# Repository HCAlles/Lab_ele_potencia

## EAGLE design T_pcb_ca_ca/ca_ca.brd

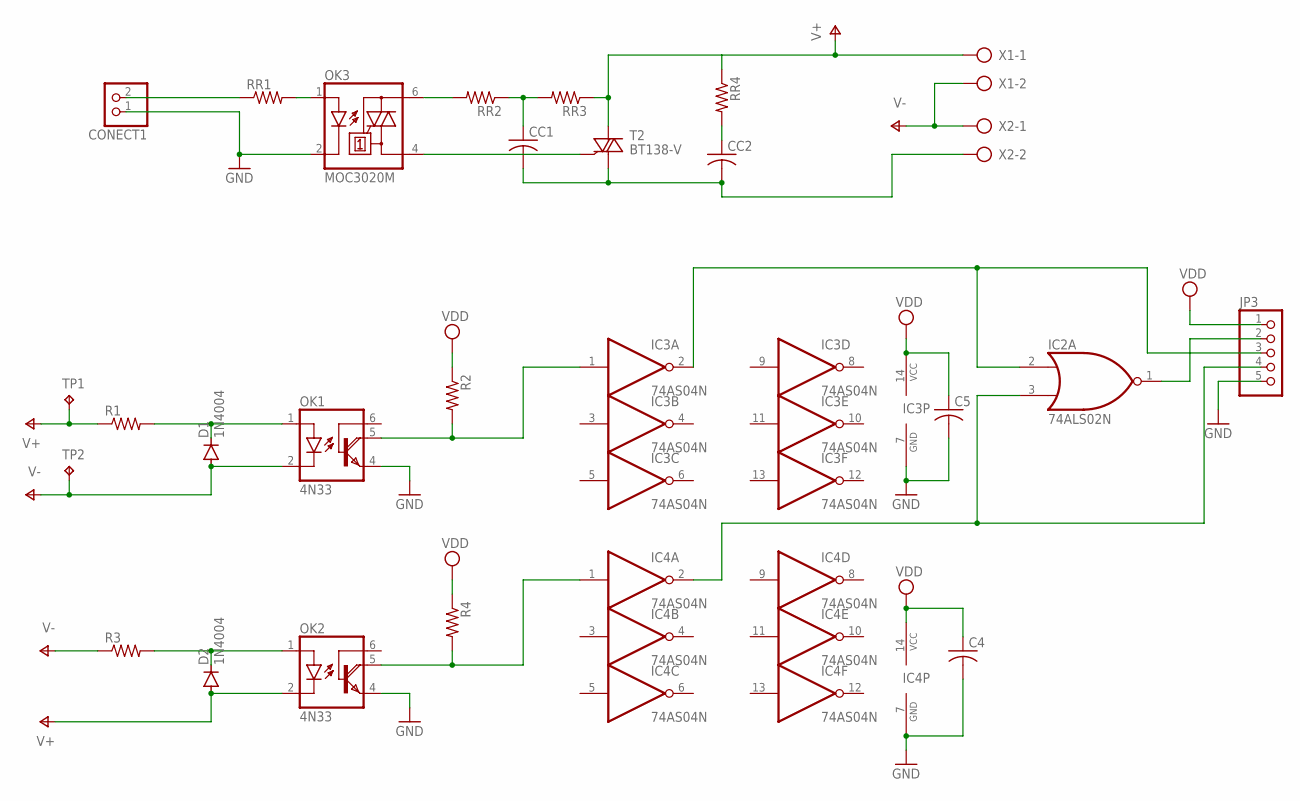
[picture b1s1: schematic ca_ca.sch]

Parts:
C4, C5: C-US102-064X133; C102-064X133
CC1, CC2: C-US102-064X133; C102-064X133
CONECT1: PINHD-1X2; 1X02
D1, D2: 1N4004; DO41-10
IC2: 74ALS02N; DIL14
IC3, IC4: 74AS04N; DIL14
JP3: PINHD-1X5; 1X05
OK1, OK2: 4N33; DIL06
OK3: MOC3020M; DIL06
R1, R2, R3, R4: R-US_0617/22; 0617/22
RR1, RR2, RR3, RR4: R-US_0617/22; 0617/22
T2: BT138-V; TO220BV
TP1, TP2: TPPAD1-17Y; P1-17Y
X1, X2: AK500/2-H

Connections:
GND: C4.2, C5.2, CONECT1.1, IC2.7 (GND), IC3.7 (GND), IC4.7 (GND), JP3.5, OK1.4 (E), OK2.4 (E), OK3.2 (C)
unnamed: OK3.1 (A), RR1.2
unnamed: CONECT1.2, RR1.1
unnamed: OK3.4 (A1), T2.G
unnamed: CC1.1, RR2.1, RR3.2
unnamed: OK3.6 (A2), RR2.2
unnamed: IC3.1 (I), OK1.5 (COL), R2.2
unnamed: CC1.2, CC2.2, T2.T1 (A1), X2.2
unnamed: CC2.1, RR4.2
unnamed: D1.C, OK1.1 (A), R1.2
unnamed: IC2.2 (I0), IC3.2 (O), JP3.3
unnamed: IC4.1 (I), OK2.5 (COL), R4.2
unnamed: D2.C, OK2.1 (A), R3.2
unnamed: IC2.3 (I1), IC4.2 (O), JP3.4
unnamed: IC2.1 (O), JP3.2
V+: D2.A, OK2.2 (C), R1.1, RR3.1, RR4.1, T2.T2 (A2), TP1.TP, X1.1
V-: D1.A, OK1.2 (C), R3.1, TP2.TP, X1.2, X2.1
VCC: IC2.14 (VCC)
VDD: C4.1, C5.1, IC3.14 (VCC), IC4.14 (VCC), JP3.1, R2.1, R4.1

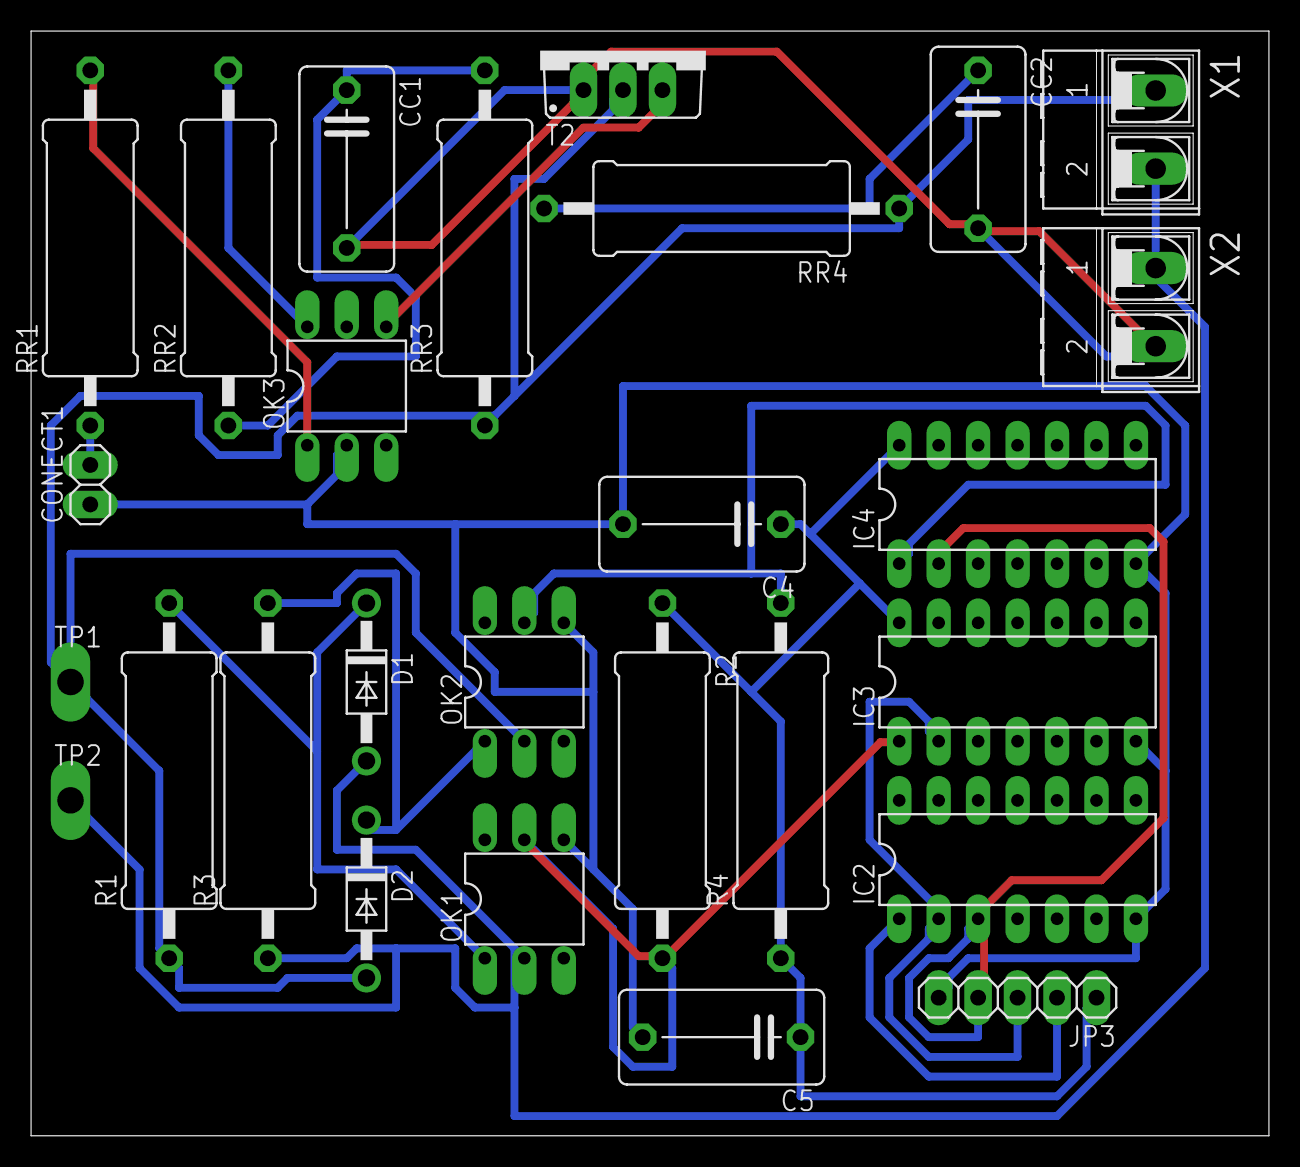
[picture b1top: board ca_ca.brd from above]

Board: 2 copper layers, 79.7 x 71.1 mm, 27 parts (0 on the bottom side), 18 nets.
